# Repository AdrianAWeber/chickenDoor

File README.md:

# chickenDoor
A Project for a automated chicken door

# Firmware

Clone the Low Power Software from
https://github.com/rocketscream/Low-Power

The .ino file in frirmware is the firmware to be compiled in Arduino IDE. 
It is tested for a Pro Micro 5V/16MHz (Arduino Leonardo)

Already compiled hex file can be found there too.

systemctl stop ModemManager

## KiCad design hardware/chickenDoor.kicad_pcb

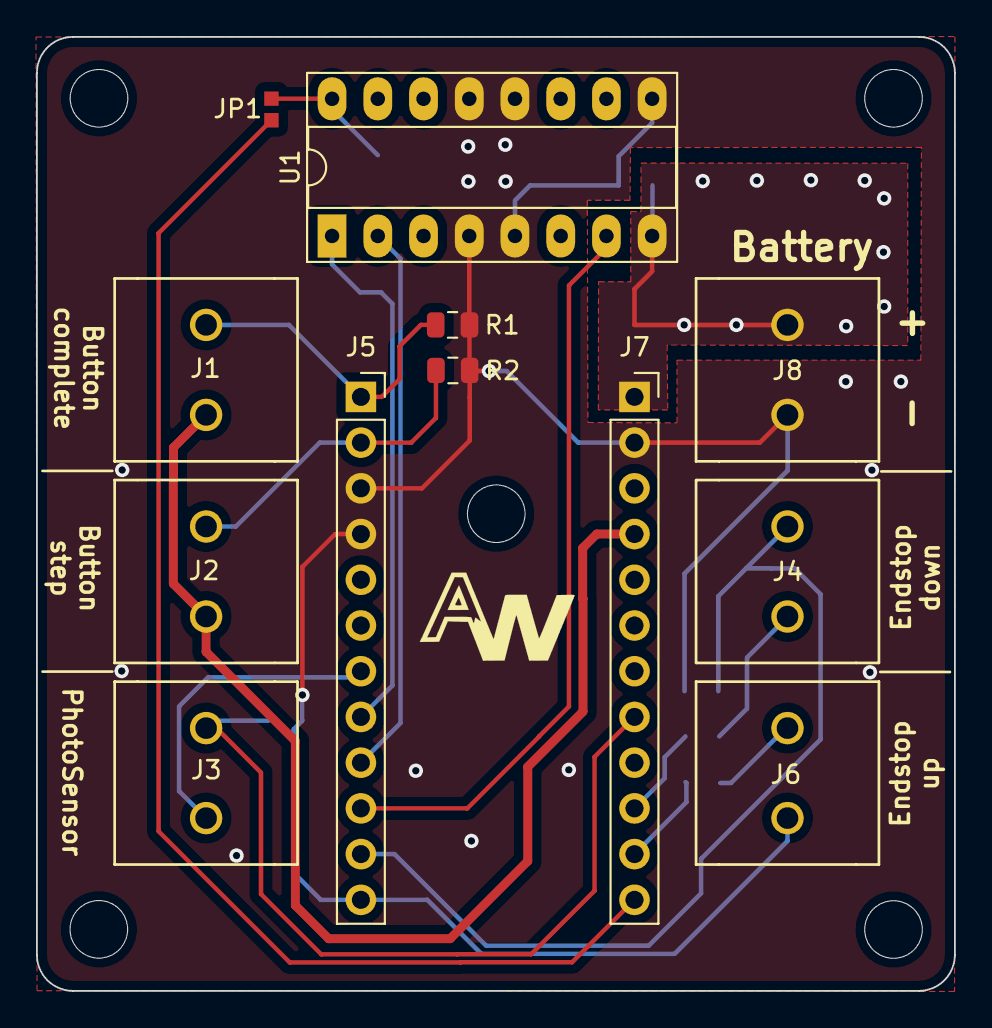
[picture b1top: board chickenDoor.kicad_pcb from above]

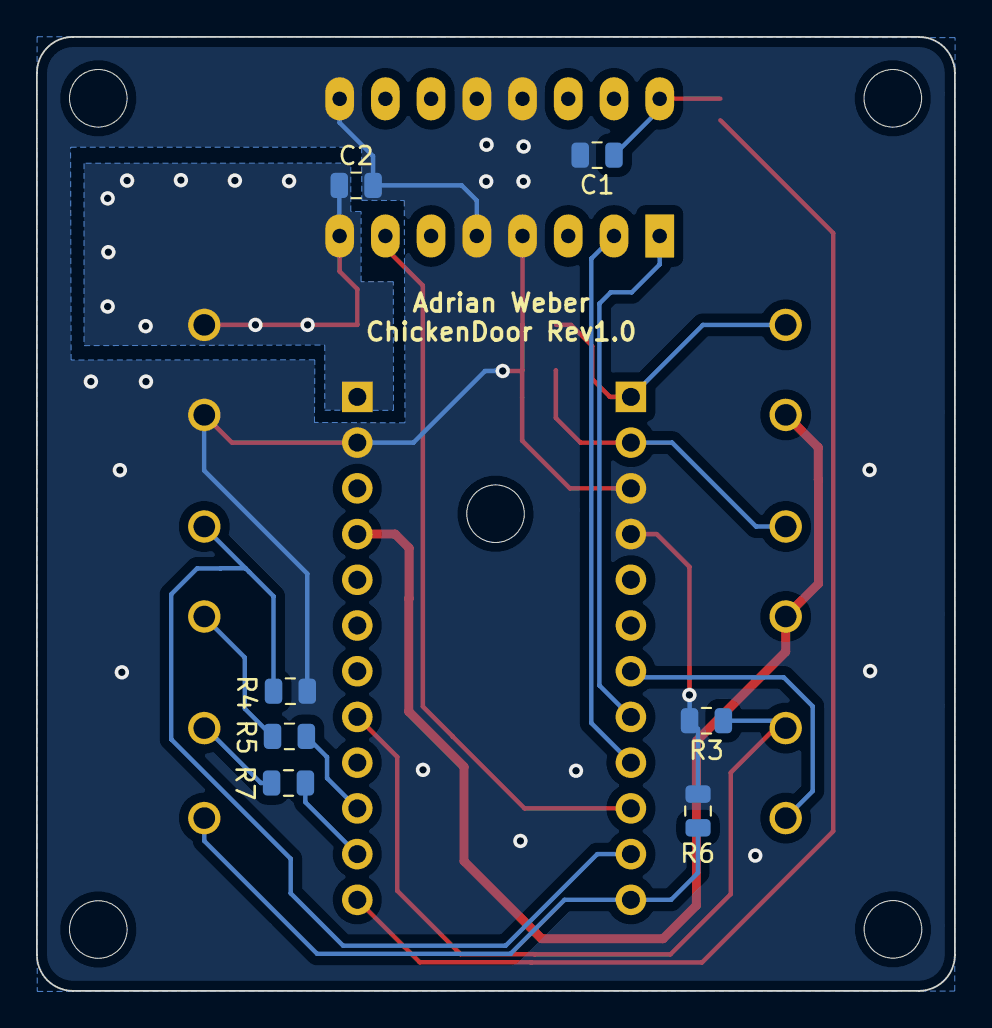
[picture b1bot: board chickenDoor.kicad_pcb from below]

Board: 2 copper layers, 51.0 x 53.0 mm, 20 parts (7 on the bottom side), 18 nets.

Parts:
C1, C2: 0.1uF; C_0805_2012Metric
J1, J2, J3, J4, J6, J8: Screw_Terminal_01x02; screwterminal
J5, J7: Conn_01x12_Female; PinSocket_1x12_P2.54mm_Vertical
JP1: SolderJumper_2_Open; 2pin
L1: Logo_Plain; Logo_8x5
R1, R2, R3, R4, R6: 4k7; R_0805_2012Metric
R5, R7: 470R; R_0805_2012Metric
U1: L293D; DIP-16_W7.62mm_Socket_LongPads

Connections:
5V_Motor_out: J7.12, JP1.2
5V_down: J7.10, R5.1
5V_up: J7.11, R7.1
+6V: C2.1, J7.1, J8.2, U1.8
End_down: J4.2, J5.11, R4.1
End_up: J5.12, J6.1, R6.1
GND: C1.2, C2.2, J5.3, J5.4, J7.2, J8.1, R1.2, R2.2, R3.2, R4.2, R6.2, U1.4, U1.5, U1.9, U1.12, U1.13
Motor_0: J5.9, U1.2
Motor_1: J5.10, U1.7
Motor_EN: J5.8, U1.1
Move_complete: J1.1, J5.1, R1.1
Move_step: J2.1, J5.2, R2.1
unnamed: C1.1, JP1.1, U1.16
unnamed: J4.1, R5.2
unnamed: J6.2, R7.2
Photo_Powr: J3.2, J5.7
Photo_Sens: J3.1, J7.8, R3.1
Vcc: J1.2, J2.2, J7.4

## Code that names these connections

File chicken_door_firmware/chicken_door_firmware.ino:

/*
 * CHICKEN DOOR AUTOMATISATION
 * 
 *  Pin 0 -> Interrupt Button_complete
 *  Pin 1 -> Interrupt Buttpn_steps
 *  Pin 2 -> Interrupt DS3231
 *  
 *  Pin 3 -> Switch opened
 *  Pin 4 -> Switch closed
 *  
 *  Pin 5 -> Motor Enable
 *  Pin 6 -> Motor connection A
 *  Pin 7 -> Motor connection B
 */

//TODO: Check if Pin 0 can be used for pin 2; otherwise fix it on PCB
//      PCB has no MOTOR Connector ...

#include <EEPROM.h>
#include <avr/sleep.h>
#include "LowPower.h"

/**
 * Digital Pins
 */
 
#define MOVE_COMPLETE 1
#define MOVE_STEP 0
#define BTN_step_read 2
#define Photo_Pwr 4
#define Motor_En 5
#define Motor_B 6
#define Motor_A 7
#define End_down 8
#define End_up 9
#define DOWN_5V 14
#define UP_5V   16
#define MOTOR_OUT_5V 10

/**
 * Analog Pins
 */
#define PR 0 // analog Pin0  -> A0 | PhotoSensor Measurement


#define TIME_OPEN  17000
#define TIME_CLOSE 11200

#define LightThreshold_close 18
#define LightThreshold_open 25

byte position_door = 0;
byte dir           = 0;  // 0: down; 1: up
byte pressed       = 0;

byte move_complete_interr = 0;
byte move_step_interr     = 1;

unsigned int light         = 1000;
unsigned int light_pre     = 1000;

//Measure not permamntly: interval can be set here 
unsigned int timecnt       = 0 ; 
unsigned int TimeIntervall = 5;//225; // Multiple of 8 sec   

void setup() {
  // Read position of door  -> Address 0
  position_door = EEPROM.read(0);  // 0 -> closed ; 1-> open
  pinMode(Motor_En, OUTPUT);
  pinMode(Motor_A, OUTPUT);
  pinMode(Motor_B, OUTPUT);
  pinMode(Photo_Pwr, OUTPUT);
  pinMode(DOWN_5V, OUTPUT);
  pinMode(UP_5V, OUTPUT);
  pinMode(MOTOR_OUT_5V, OUTPUT);

  digitalWrite(Motor_En,LOW); // Stop
  digitalWrite(Motor_A,LOW);   // Save power
  digitalWrite(Motor_B,LOW);
  digitalWrite(Photo_Pwr,LOW);
  digitalWrite(DOWN_5V,LOW);
  digitalWrite(UP_5V,LOW);
  digitalWrite(MOTOR_OUT_5V,LOW);
     
  attachInterrupt(digitalPinToInterrupt(MOVE_COMPLETE), move_complete_ISR, RISING);
  attachInterrupt(digitalPinToInterrupt(MOVE_STEP), move_step_ISR, RISING);
  //Serial.begin(9600);
}

void loop() {

//LowPower.idle(SLEEP_8S, ADC_OFF, TIMER4_OFF, TIMER3_OFF, TIMER1_OFF, TIMER0_OFF, SPI_OFF, USART1_OFF, TWI_OFF, USB_OFF);
  LowPower.powerDown(SLEEP_8S, ADC_OFF, BOD_OFF);  
  timecnt++;

  if (move_complete_interr == 1){ // Move by Button: complete move to end
    if (position_door == 1){ // open
      close_door(TIME_CLOSE,1);
    } else {
      open_door(TIME_OPEN,1);
    }
    move_complete_interr = 0;
    move_step_interr = 0;
    if (timecnt >= TimeIntervall) {
     timecnt = 0;
    }
  } else if(move_step_interr == 1) {  // Move by Button: Just as lang as button is holded; Stopped by Reeds

    if (dir == 0){
      down();
      dir = 1;
    } else {
      up();
      dir = 0;
    }
    digitalWrite(Motor_En, HIGH);
    while (move_step_interr == 1) {
      delay(200);
      move_step_interr = digitalRead(MOVE_STEP);//digitalRead(BTN_step_read);
        
      /*if ((move_step_interr == 1)) {
        int endPos = 0;
        if (dir == 1) endPos = digitalRead(End_down); // moving down
        if (dir == 0) endPos = digitalRead(End_up);
        if (endPos == 1) move_step_interr = 0; // break loop due to End of door
      }*/
    }

    // Stop Motor again
    digitalWrite(Motor_En,LOW); // Stop
    digitalWrite(Motor_A,LOW);   // Save power
    digitalWrite(Motor_B,LOW);
    digitalWrite(MOTOR_OUT_5V,LOW);

    //Unpower the Reeds
    //if (STOP_BY_SENSOR == 1) { 
      digitalWrite(DOWN_5V,LOW);
      digitalWrite(UP_5V,LOW);
    //}
     
    move_complete_interr = 0;
    move_step_interr = 0;
    if (timecnt >= TimeIntervall) {
      timecnt = 0;
    }
 
  } else {  //Move by Ligh Sensor
    if (timecnt >= TimeIntervall) {
      digitalWrite(Photo_Pwr,HIGH); delay(100);
      light = analogRead(PR); delay (100);
      digitalWrite(Photo_Pwr,LOW);

      // evening
      if (light <= LightThreshold_close && light_pre > LightThreshold_close && position_door == 1){
        int timeOutVar = close_door(TIME_CLOSE,1);
        if ( timeOutVar > 0) { // first try did not work out.
          close_door_ifTimeout(TIME_CLOSE,0); // close by time. Inverted due to order on line
        }
      } else if (light > LightThreshold_open && light_pre <= LightThreshold_open && position_door == 0) {
         if (open_door(TIME_OPEN,1) == 1){ // Timeout!
           // TODO: Do something in case of timeout
         }
      }
      
      light_pre = light;
     
      move_complete_interr = 0;
      move_step_interr = 0;
      timecnt = 0;
    }
  }
}//loop


// open the door
byte open_door(unsigned int open_time, unsigned int STOP_BY_SENSOR){
  //Motor Settings for upwards
  up();

  byte timeoutFlag = 0;
 
  // enable Motor
  digitalWrite(Motor_En, HIGH);

  if (STOP_BY_SENSOR == 1) {
    bool endPos = 0;
    unsigned int cntTime = 0;
    while (endPos == 0){
      endPos = digitalRead(End_up);
      delay(5); // 5ms;
      cntTime++;
      if (cntTime > 6000) {// ~30 sek; Timeout
        timeoutFlag = 1;
        break; 
      }
    }
  } else { // stop by time
    delay(open_time);
  }
  
  digitalWrite(Motor_En,LOW); // Stop
  digitalWrite(Motor_A,LOW);  // Save power
  digitalWrite(Motor_B,LOW);
  digitalWrite(MOTOR_OUT_5V,LOW);

  //Unpower the Reeds
  //if (STOP_BY_SENSOR == 1) { 
    digitalWrite(DOWN_5V,LOW);
    digitalWrite(UP_5V,LOW);
 // }

  // Save status to EEPROM
  // Even if timeout is active, door is most likely open as no sideflip of string is possible.
  EEPROM.write(0,1); // open
  position_door = 1;

  return timeoutFlag;
}


// close door if Timeout
byte close_door_ifTimeout(unsigned int open_time, unsigned int STOP_BY_SENSOR){
  //Motor Settings for upwards
  up();

  byte timeoutFlag = 0;
 
  // enable Motor
  digitalWrite(Motor_En, HIGH);

  if (STOP_BY_SENSOR == 1) {
    bool endPos = 0;
    unsigned int cntTime = 0;
    while (endPos == 0){
      endPos = digitalRead(End_up);
      delay(5); // 5ms;
      cntTime++;
      if (cntTime > 6000) {// ~30 sek; Timeout
        timeoutFlag = 1;
        break; 
      }
    }
  } else { // stop by time
    delay(open_time);
  }
  
  digitalWrite(Motor_En,LOW); // Stop
  digitalWrite(Motor_A,LOW);  // Save power
  digitalWrite(Motor_B,LOW);
  digitalWrite(MOTOR_OUT_5V,LOW);

  //Unpower the Reeds
  //if (STOP_BY_SENSOR == 1) { 
    digitalWrite(DOWN_5V,LOW);
    digitalWrite(UP_5V,LOW);
 // }

  // Save status to EEPROM
  // Even if timeout is active, door is most likely open as no sideflip of string is possible.
  EEPROM.write(0,0); // close
  position_door = 0;

  return timeoutFlag;
}


//close the door
byte close_door(unsigned int closeTime, unsigned int STOP_BY_SENSOR){
  // Motor Setting to close door
  down();

  byte timeoutFlag = 0;  // O: Closed; 1: opened again; 2: Timeout
  
  // enable Motor
  digitalWrite(Motor_En, HIGH);

  if (STOP_BY_SENSOR == 1) {
    bool endPos = 0;
    unsigned int cntTime = 0;
    while (endPos == 0){
      endPos = digitalRead(End_down);
      if (endPos == 1) {
        timeoutFlag = 0;
        break;
      } else {
        if (cntTime > 600) {  //~ 3sek to avoid measurement in open position.
          endPos = digitalRead(End_up);
          if (endPos == 1) {
            timeoutFlag = 1; // again in opened position;
            endPos = 1;
            break;
          }
        }
      }
      delay(5); // 5ms;
      cntTime++;
      if (cntTime > 6000) {// ~30 sek; Timeout
        timeoutFlag = 2;
        endPos = 1;
        break; 
      }
    }
  } else { // stop by time
    delay(closeTime);
  }
  
  // Stop Motor again
  digitalWrite(Motor_En,LOW); // Stop
  digitalWrite(Motor_A,LOW);  // Save power
  digitalWrite(Motor_B,LOW);
  digitalWrite(MOTOR_OUT_5V,LOW);

  //Unpower the Reeds
  //if (STOP_BY_SENSOR == 1) { 
    digitalWrite(DOWN_5V,LOW);
    digitalWrite(UP_5V,LOW);
  //}  

  // Save status to EEPROM
  if (timeoutFlag == 0) {
    EEPROM.write(0,0); // closed
    position_door = 0;
  } else if (timeoutFlag == 1){
    EEPROM.write(0,1); // open
    position_door = 1;
  } else { // Timeout: we think we are open.
    EEPROM.write(0,1); // open
    position_door = 1;
  }

  return timeoutFlag; 
}

void up(){
  digitalWrite(MOTOR_OUT_5V,HIGH);
   // Motor will turn right
  digitalWrite(Motor_A,HIGH);   
  digitalWrite(Motor_B,LOW);

  //power the upwards Reed 
  //if (STOP_BY_SENSOR == 1) 
  digitalWrite(UP_5V,HIGH);
  digitalWrite(DOWN_5V,HIGH);
}

void down(){
  digitalWrite(MOTOR_OUT_5V,HIGH);
   // Motor will turn left
  digitalWrite(Motor_A,LOW);   
  digitalWrite(Motor_B,HIGH);

  //power the downwards Reed 
  //if (STOP_BY_SENSOR == 1) 
  digitalWrite(DOWN_5V,HIGH);
  digitalWrite(UP_5V,HIGH);
}

void move_complete_ISR(){
  move_complete_interr = 1;
}

void move_step_ISR(){
  move_step_interr = 1;
}

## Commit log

2020-08-15 3d Files for the motor Holder and the PCB Holder
2020-08-15 firmware for chicken door and small howto
2020-08-15 PCB files
2020-08-15 logo
2020-10-31 firmware: layout and typos
2020-10-31 fix: Retry and safety solution for case of a non working stop sensor
2020-12-16 bux fix
